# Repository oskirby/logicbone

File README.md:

LogicBone
=========

When you can't quite find the development board you want, why not make your own?

This project aims to design a feature rich FPGA development board that is
compatible with the open source FPGA synthesis tools such as [yosys](http://www.clifford.at/yosys/),
[NextPNR](https://github.com/YosysHQ/nextpnr) and [SymbiFlow](https://github.com/SymbiFlow),
while also targeting larger logic designs that need faster IO. The
requirements set out for this board are, in order of priority:
 * Compatiblity with open-source FPGA synthesis tools.
 * Minimum of 4Gb of high speed memory, preferably at least 8Gb.
 * At least one Ethernet interface.
 * Compatiblity with existing expansion interfaces.
 * USB interface for programming, debug and power.
 * Licenseable as Open Source Hardware.

The ultimate objective of this board is to instantiate a soft core processor, such as
the RISC-V, and use it to boot a Linux operating system with networking.

To that effect, this board is designed to be mechanically and electrically compatible
with the Beaglebone Black, but featuring a Lattice ECP5 FPGA, which is available in
logic sizes up to 85k LUTs, and a selection of hardware blocks for DDR3 DQS acceleration,
MIPI interfaces, DSPs and 3Gbps SERDES.

Features
--------

The major features of this board include:
 * Lattice ECP5 (LFE5UM5G-45F-8BG381C)
   - 44k LUTs and 351 kbits of distributed RAM 
   - 1944 kbits of embedded block RAM
   - 203 IO pins
   - 72 hardware multipliers
   - 4 PLLs
   - 2 dual channel 5Gbps SERDES
 * Beaglebone Black mechanical and header compatibility.
   - P9 is fully connected to the FPGA.
   - P8 has 32 pins connected to the FPGA.
   - 12-bit 1MSPS muxed ADC on P9 analog pins.
 * 8Gb on-board DDR3L RAM
 * KSZ9031 Gigabit Ethernet PHY
 * microSD card slot
 * USB-C upstream facing port for power and programming
 * USB-C downstream facing port with USB Superspeed support
 * M.2 E-Keyed expansion interface:
   - Accepts connectivity options in the 2230 form factor
   - Both PCIe lanes are routed to the FPGA SERDES
   - GPIO, UART, SDIO and PCM interfaces
 * MaxLinear MxL7704 power manager

Work In Progress
----------------
This project has completed the PCB layout phase, and we are moving into hardware
prototyping. While we wait for the first boards to arrive, we have a 
[schematic](logicbone.pdf) and some renders of the board that might satisfy your
curiosity.

We would be happy to accept any feedback and review on the design that you
might be willing to provide.

Copyright
---------
Copyright Owen Kirby 2020

This documentation describes Open Hardware and is licensed under the
CERN OHL v1.2.

You may redistribute and modify this documentation under the terms of
the CERN OHL v1.2. (see [LICENSE.txt](LICENSE.txt)). This documentation
is distributed WITHOUT ANY EXPRESS OR IMPLIED WARRANTY, INCLUDING OF
MERCHANTABILITY, SATISFACTORY QUALITY AND FITNESS FOR A PARTICULAR
PURPOSE. Please see the CERN OHL v.1.2 for applicable conditions.

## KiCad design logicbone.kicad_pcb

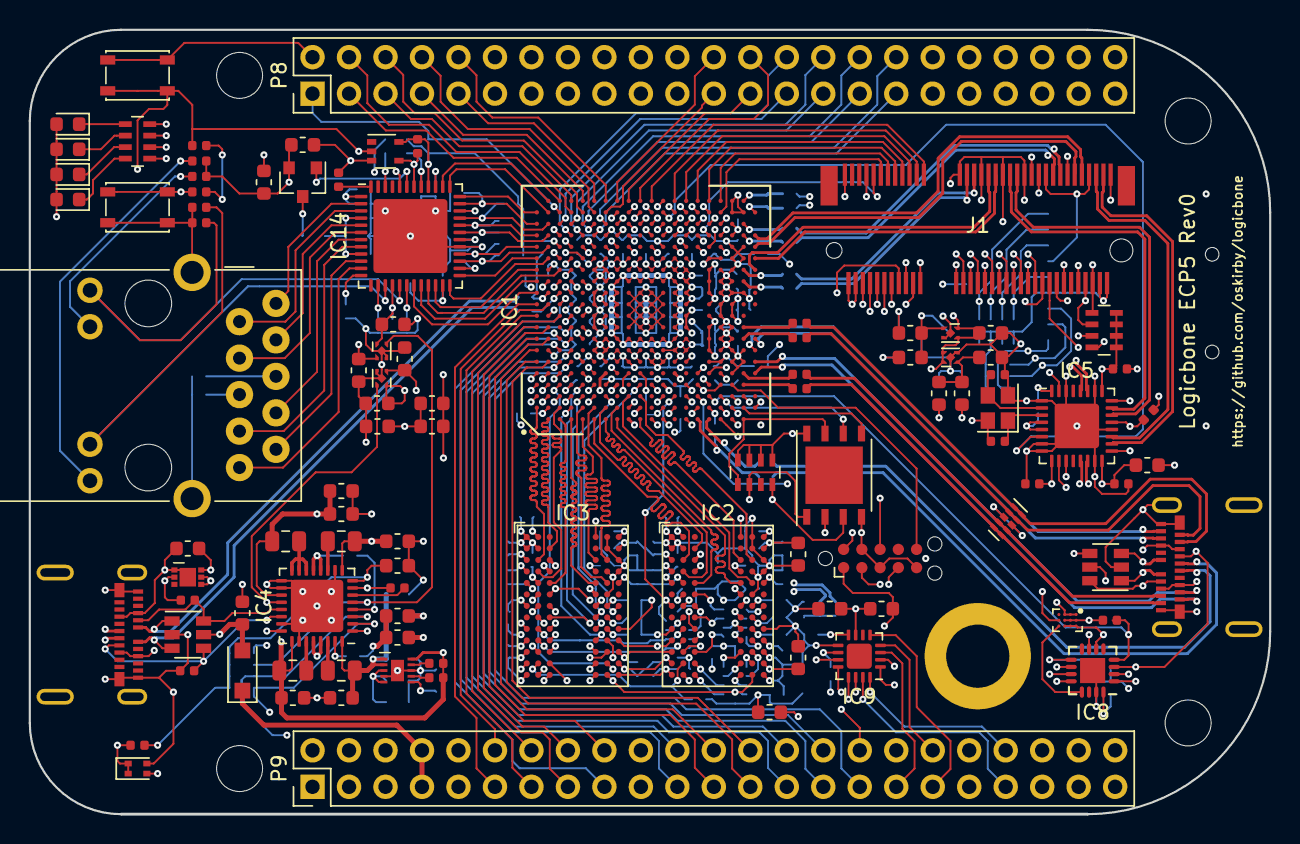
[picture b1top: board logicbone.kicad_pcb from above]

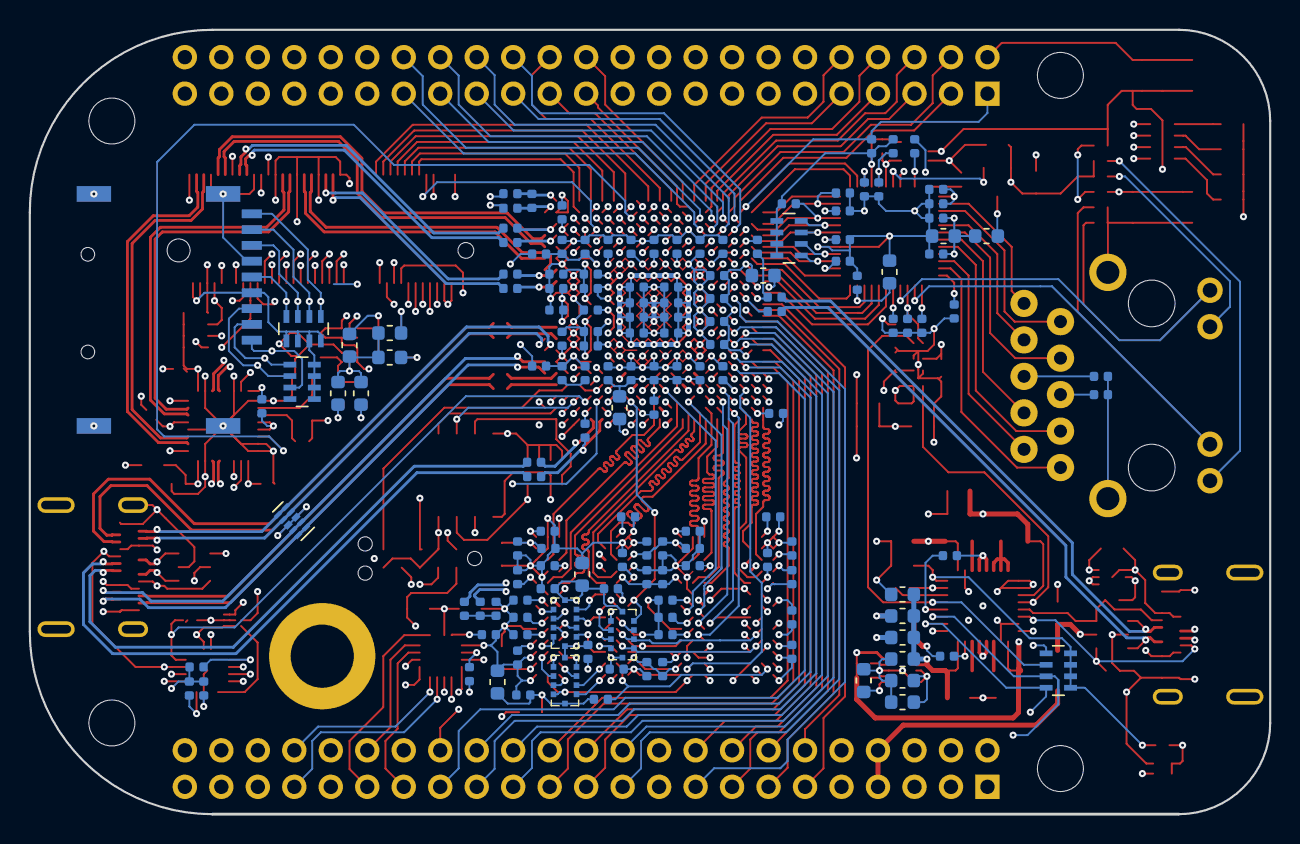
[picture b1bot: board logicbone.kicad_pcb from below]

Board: 8 copper layers, 86.4 x 54.6 mm, 255 parts (150 on the bottom side), 310 nets.

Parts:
C1, C108, C109: C_Small; C_0402_1005Metric
C2, C3, C8, C9, C10, C11, C110, C111, C112, C113, C114, C115, C116, C118, C120, C121, C122, C123, C201, C202, C210, C211, C221, C222, C230, C231, C257, C260, C261, C264, C265, C266, C280, C300, C301, C302, C309, C310, C311, C316, C317, C318, C319, C401, C402, C403, C411, C412, C421, C422, C423, C431, C432, C451, C452, C454, C455, C456, C461, C462, C463, C464, C465, C467, C469, C500, C501, C502, C504, C514, C517, C522, C527: 100nF; C_0402_1005Metric
C4, C258, C404, C405, C406, C414, C415, C416, C424, C425, C426, C434, C435, C436, C505, C506, C508, C509, C512, C513, C515, C516, C520, C521, C525, C526: 10nF; C_0402_1005Metric
C5, C100, C101, C102, C104, C117, C150, C151, C152, C154, C155, C156, C158, C159, C160, C161, C162, C163, C164, C165, C166, C167, C170, C171, C255, C303, C304, C308, C315, C400, C410, C420, C430, C440, C441, C442, C443, C445, C460, C524, C529: 10uF; C_0603_1608Metric
C6, C259, C305, C306, C307, C312, C313, C314: 1nF; C_0402_1005Metric
C7: 1uF; C_0603_1608Metric
D1: LED_Dual_ACAC; LED_0603_DUAL
D2, D3, D4, D5: LED_ALT; LED_0603_1608Metric
D6: D_Schottky_ALT; D_SOD-123F
D7, D8: D5V0F4U6SO; SOT-23-6
D9, D10: TPD4E02B04; USON-10_2.5x1.0mm_P0.5mm
FB1, FB2, FB3, FB4, FB5, FB7, FB8, FB9: MPZ1608S600; L_0603_1608Metric
H1, H2, H3, H4: MountingHole; MountingHole_3.2mm_M3
H5: MountingHole_Pad; wurth-9774025360
IC1: ECP5UM-CABGA381; caBGA-381_20x20_17.0x17.0mm
IC2, IC3: DDR3-TFBGA78; FBGA-78_7.5x11mm_Layout2x3x13_P0.8mm
IC4: MXL7704; QFN-32-1EP_5x5mm_P0.5mm_EP3.65x3.65mm
IC5: PI6CG18401; QFN-32-1EP_5x5mm_P0.5mm_EP3.1x3.1mm
IC6: NCP349; DFN6_1.6x2mm
IC7: FPF2595; WLCSP-12_3x4_1.3x1.8mm
IC8: FUSB307; UQFN-16-1EP_3x3mm_P0.5mm_EP1.75x1.75mm
IC9: TLA2518; WQFN-16-1EP_3x3mm_P0.5mm_EP1.75x1.75mm
IC10: AT25SL128A; DFN-8-1EP_6x5mm_P1.27mm_EP4x4mm
IC12: 74LVC1G07; SOT-353_SC-70-5
IC13: TPS51206; WSON-10EP-2x2mm
IC14: KSZ9031RNXCA; QFN-48-1EP_7x7mm_P0.5mm_EP5.15x5.15mm
IC17, IC18: NCP110AMX110; UDFN-4-1EP_1x1mm_P0.65mm_EP0.48x0.48mm
IC19, IC20: NCP115AMX250; UDFN-4-1EP_1x1mm_P0.65mm_EP0.48x0.48mm
J1: NGFF-KEY-E; TE-2199119-4
J2, J5: USB_C_Receptacle; Molex-1054500101
J3: ARJM11xx-502; ARJM11B1_502
J4: TC2050-IDC-NL; Tag-Connect_TC2050-IDC-NL_2x05_P1.27mm_Vertical
J6: Micro_SD_MEM2075; MEM2075
L1: 2.2uH; L_0805_2012Metric
L2, L4: 0.47uH; L_0805_2012Metric
L3: 1uH; L_0805_2012Metric
P8, P9: BB_2x23; PinHeader_2x23_P2.54mm_Vertical
Q1: Q_PMOS_GSD; SOT-23
R1, R2, R6, R37: 20; R_0402_1005Metric
R3, R4: 240; R_0402_1005Metric
R5: 100; R_0402_1005Metric
R7: 12.1k; R_0402_1005Metric
R8, R13, R18, R20, R21, R22, R23, R24, R25, R30, R31, R32, R35: 10k; R_0402_1005Metric
R9, R14, R15, R16: 47; R_0402_1005Metric
R10: 470; R_0402_1005Metric
R11, R12: 5.1k; R_0402_1005Metric
R17, R26: 1.5k; R_0402_1005Metric
R19, R29: 4.7k; R_0402_1005Metric
R27, R28: R; R_0402_1005Metric
R33: 750; R_0402_1005Metric
R34, R36: 1.2k; R_0402_1005Metric
RN1, RN2, RN3: 47; EXBD-1206
RN4, RN5, RN7: 4.7k; R_Array_Concave_4x0603
RN6, RN8, RN11: 10k; R_Array_Concave_4x0603
RN9: 470; R_Array_Concave_4x0603
SW1, SW2: SW_SPST; SW_SPST_PTS810
Y1: 25MHz; Crystal_SMD_2520-4Pin_2.5x2.0mm

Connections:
+3V3: C100.1, IC4.1, IC4.8, R10.2, R19.1, R29.1, RN5.5, RN5.6, RN5.7, RN5.8
/DDR3 Power/VDDR_CORE: C400.1, C401.1, C402.1, C403.1, C404.1, C405.1, C406.1, C420.1, C421.1, C422.1, C423.1, C424.1, C425.1, C426.1, FB9.2, IC2.A2, IC2.A9, IC2.D7, IC2.G2, IC2.G8, IC2.K1, IC2.K9, IC2.M1, IC2.M9, IC3.A2, IC3.A9, IC3.D7, IC3.G2, IC3.G8, IC3.K1, IC3.K9, IC3.M1, IC3.M9
/DDR3 Power/VDDR_IO: C410.1, C411.1, C412.1, C414.1, C415.1, C416.1, C430.1, C431.1, C432.1, C434.1, C435.1, C436.1, FB8.2, IC2.B9, IC2.C1, IC2.E2, IC2.E9, IC3.B9, IC3.C1, IC3.E2, IC3.E9
/Ethernet/25M_REFCLK: C2.1, IC1.M19, IC5.6
/Ethernet/ETH_1V2: C308.1, C309.1, C310.1, C311.1, C312.1, C313.1, C314.1, FB7.2, IC14.14, IC14.18, IC14.23, IC14.26, IC14.30, IC14.39, Q1.3
/Ethernet/ETH_AVDDL: C315.1, C316.1, C317.1, FB7.1, IC14.4, IC14.9, IC14.44
/Ethernet/ETH_LDO: IC14.43, Q1.1
/Ethernet/ETH_LED_L: IC14.15, J3.L2, R24.2
/Ethernet/ETH_LED_R: IC14.17, J3.L4, R25.2
/Ethernet/ETH_REFCLK: IC1.D12, IC14.41, R21.2, R22.2
/Ethernet/ETH_RXCLK: IC1.A18, IC14.35, R23.2
/Ethernet/ETH_RXCTL: IC1.B18, IC14.33, R20.2
/Ethernet/ETH_RXD0: IC1.A17, IC14.32, RN11.4
/Ethernet/ETH_RXD1: IC1.B17, IC14.31, RN11.3
/Ethernet/ETH_RXD2: IC1.A16, IC14.28, RN11.2
/Ethernet/ETH_RXD3: IC1.B16, IC14.27, RN11.1
/Ethernet/ETH_TRXD1N: IC14.3, J3.2
/Ethernet/ETH_TRXD1P: IC14.2, J3.1
/Ethernet/ETH_TRXD2N: IC14.6, J3.4
/Ethernet/ETH_TRXD2P: IC14.5, J3.3
/Ethernet/ETH_TRXD3N: IC14.8, J3.8
/Ethernet/ETH_TRXD3P: IC14.7, J3.7
/Ethernet/ETH_TRXD4N: IC14.11, J3.10
/Ethernet/ETH_TRXD4P: IC14.10, J3.9
/Ethernet/ETH_TXCLK: IC1.B15, IC14.24
/Ethernet/ETH_TXCTL: IC1.A15, IC14.25
/Ethernet/ETH_TXD0: IC1.A12, IC14.19
/Ethernet/ETH_TXD1: IC1.A13, IC14.20
/Ethernet/ETH_TXD2: IC1.C14, IC14.21
/Ethernet/ETH_TXD3: IC1.A14, IC14.22
/Ethernet/FPGA_USB+: D7.1, J2.A6, J2.B6, R1.1
/Ethernet/FPGA_USB-: D7.3, J2.A7, J2.B7, R2.1
/Ethernet/FPGA_USB_PULL: IC1.C16, R26.2
/Ethernet/LED_USER1: IC1.D16, J1.6, RN9.8
/Ethernet/LED_USER2: IC1.C15, J1.16, RN9.7
/Ethernet/LED_USER3: IC1.C13, RN9.6
/Ethernet/LED_USER4: IC1.B13, RN9.5
/Ethernet/MDIO_CLK: IC1.A19, IC14.36
/Ethernet/MDIO_DATA: IC1.B19, IC14.37
/Ethernet/MMC_CLK: IC1.E11, J6.5, RN6.4
/Ethernet/MMC_CMD: IC1.D15, J6.3, RN8.6
/Ethernet/MMC_DAT0: IC1.D13, J6.7, RN6.3
/Ethernet/MMC_DAT1: IC1.E13, J6.8, RN6.2
/Ethernet/MMC_DAT2: IC1.E15, J6.1, RN8.7
/Ethernet/MMC_DAT3: IC1.E14, J6.2, RN8.5
/Ethernet/MMC_DET: IC1.D14, J6.9, RN6.1
/Ethernet/~ETH_INT: IC1.B20, IC14.38
/Ethernet/~ETH_RESET: IC1.C17, IC12.4, IC14.42, R13.2
/Ethernet/~SYS_RESET: IC1.W3, IC12.2, J4.10, P9.10, R19.2, SW2.1
/Exp Headers/ADC_MISO: IC1.E8, IC9.12
/Exp Headers/ADC_MOSI: IC1.D10, IC9.14
/Exp Headers/ADC_SCLK: IC1.E9, IC9.13
/Exp Headers/P8_LVDS1n: IC1.D19, P8.4
/Exp Headers/P8_LVDS1p: IC1.C20, P8.3
/Exp Headers/P8_LVDS2n: IC1.E19, P8.6
/Exp Headers/P8_LVDS2p: IC1.D20, P8.5
/Exp Headers/P8_LVDS3n: IC1.F19, P8.8
/Exp Headers/P8_LVDS3p: IC1.E20, P8.7
/Exp Headers/P8_LVDS4n: IC1.G20, P8.10
/Exp Headers/P8_LVDS4p: IC1.F20, P8.9
/Exp Headers/P8_LVDS5n: IC1.H20, P8.24
/Exp Headers/P8_LVDS5p: IC1.G19, P8.23
/Exp Headers/P8_LVDS6n: IC1.K20, P8.26
/Exp Headers/P8_LVDS6p: IC1.J20, P8.25
/Exp Headers/P8_LVDS7n: IC1.D17, P8.28
/Exp Headers/P8_LVDS7p: IC1.C18, P8.27
/Exp Headers/P8_LVDS8n: IC1.E17, P8.30
/Exp Headers/P8_LVDS8p: IC1.D18, P8.29
/Exp Headers/P8_LVDS9n: IC1.F18, P8.32
/Exp Headers/P8_LVDS9p: IC1.E18, P8.31
/Exp Headers/P8_LVDS10n: IC1.G18, P8.34
/Exp Headers/P8_LVDS10p: IC1.F17, P8.33
/Exp Headers/P8_LVDS11n: IC1.F16, P8.36
/Exp Headers/P8_LVDS11p: IC1.E16, P8.35
/Exp Headers/P8_LVDS12n: IC1.H16, P8.38
/Exp Headers/P8_LVDS12p: IC1.G16, P8.37
/Exp Headers/P8_LVDS13n: IC1.J16, P8.40
/Exp Headers/P8_LVDS13p: IC1.J17, P8.39
/Exp Headers/P8_LVDS14n: IC1.H17, P8.42
/Exp Headers/P8_LVDS14p: IC1.H18, P8.41
/Exp Headers/P8_LVDS15n: IC1.K19, P8.44
/Exp Headers/P8_LVDS15p: IC1.J19, P8.43
/Exp Headers/P8_LVDS16n: IC1.K18, P8.46
/Exp Headers/P8_LVDS16p: IC1.J18, P8.45
/Exp Headers/P9_AIN0: IC9.15, P9.39
/Exp Headers/P9_AIN1: IC9.16, P9.40
/Exp Headers/P9_AIN2: IC9.1, P9.37
/Exp Headers/P9_AIN3: IC9.2, P9.38
/Exp Headers/P9_AIN4: IC9.3, P9.33
/Exp Headers/P9_AIN5: IC9.4, P9.36
/Exp Headers/P9_AIN6: IC9.5, P9.35
/Exp Headers/P9_CLKOUT: IC1.B10, P9.41
/Exp Headers/P9_GPIO11: IC1.A11, P9.11
/Exp Headers/P9_GPIO12: IC1.B11, P9.12
/Exp Headers/P9_GPIO13: IC1.A10, P9.13
/Exp Headers/P9_GPIO14: IC1.C10, P9.14
/Exp Headers/P9_GPIO15: IC1.A9, P9.15
/Exp Headers/P9_GPIO16: IC1.B9, P9.16
/Exp Headers/P9_GPIO17: IC1.C11, P9.17
/Exp Headers/P9_GPIO18: IC1.A8, P9.18
/Exp Headers/P9_GPIO21: IC1.D9, P9.21
/Exp Headers/P9_GPIO22: IC1.C8, P9.22
/Exp Headers/P9_GPIO23: IC1.B8, P9.23
/Exp Headers/P9_GPIO24: IC1.A7, P9.24
/Exp Headers/P9_GPIO25: IC1.A6, P9.25
/Exp Headers/P9_GPIO26: IC1.B6, P9.26
/Exp Headers/P9_GPIO27: IC1.D8, P9.27
/Exp Headers/P9_GPIO42: IC1.E10, P9.42
/Exp Headers/P9_SPI_D0: IC1.D7, P9.29
/Exp Headers/P9_SPI_D1: IC1.C6, P9.30
/Exp Headers/P9_SPI_SCLK: IC1.D6, P9.31
/Exp Headers/PWR_BUTTON: IC1.U2, P9.9, R29.2, SW1.1
/Exp Headers/SCL: IC1.U1, IC4.3, IC5.10, IC8.12, J1.60, P9.19, RN5.3
/Exp Headers/SDA: IC1.V1, IC4.2, IC5.11, IC8.11, J1.58, P9.20, RN5.4
/Exp Headers/SYS_5V: D6.1, P9.7, P9.8
/Exp Headers/~ADC_CSEL: IC1.E6, IC9.11
/Exp Headers/~P9_SPI_CSEL: IC1.C7, P9.28
/FPGA Memory/DDR3_A0: IC1.B4, IC2.K3, IC3.K3, RN3.3
/FPGA Memory/DDR3_A1: IC1.F4, IC2.L7, IC3.L7, RN2.2
/FPGA Memory/DDR3_A2: IC1.A4, IC2.L3, IC3.L3, RN1.9
/FPGA Memory/DDR3_A3: IC1.F3, IC2.K2, IC3.K2, RN3.9
/FPGA Memory/DDR3_A4: IC1.E5, IC2.L8, IC3.L8, RN2.8
/FPGA Memory/DDR3_A5: IC1.C5, IC2.L2, IC3.L2, RN3.2
/FPGA Memory/DDR3_A6: IC1.C4, IC2.M8, IC3.M8, RN2.9
/FPGA Memory/DDR3_A7: IC1.A5, IC2.M2, IC3.M2, R14.2
/FPGA Memory/DDR3_A8: IC1.A3, IC2.N8, IC3.N8, RN2.6
/FPGA Memory/DDR3_A9: IC1.B5, IC2.M3, IC3.M3, RN2.4
/FPGA Memory/DDR3_A10: IC1.G3, IC2.H7, IC3.H7, RN1.4
/FPGA Memory/DDR3_A11: IC1.D5, IC2.M7, IC3.M7, RN2.3
/FPGA Memory/DDR3_A12: IC1.D2, IC2.K7, IC3.K7, RN1.3
/FPGA Memory/DDR3_A13: IC1.F5, IC2.N3, IC3.N3, RN2.5
/FPGA Memory/DDR3_A14: IC1.D3, IC2.N7, IC3.N7, RN2.7
/FPGA Memory/DDR3_A15: IC1.E3, IC2.J7, IC3.J7, RN1.8
/FPGA Memory/DDR3_BA0: IC1.B3, IC2.J2, IC3.J2, RN3.8
/FPGA Memory/DDR3_BA1: IC1.H5, IC2.K8, IC3.K8, RN1.2
/FPGA Memory/DDR3_BA2: IC1.N2, IC2.J3, IC3.J3, RN3.5
/FPGA Memory/DDR3_CK+: IC1.M4, IC2.F7, IC3.F7, R15.2
/FPGA Memory/DDR3_CK-: IC1.N5, IC2.G7, IC3.G7, R16.1
/FPGA Memory/DDR3_CKE: IC1.K4, IC2.G9, IC3.G9, RN1.5
/FPGA Memory/DDR3_DM0: IC1.L4, IC2.A7
/FPGA Memory/DDR3_DM1: IC1.J5, IC3.A7
/FPGA Memory/DDR3_DQ0: IC1.G2, IC2.B3
/FPGA Memory/DDR3_DQ1: IC1.K1, IC2.C7
/FPGA Memory/DDR3_DQ2: IC1.F1, IC2.C2
/FPGA Memory/DDR3_DQ3: IC1.K3, IC2.C8
/FPGA Memory/DDR3_DQ4: IC1.H2, IC2.E3
/FPGA Memory/DDR3_DQ5: IC1.J3, IC2.E8
/FPGA Memory/DDR3_DQ6: IC1.G1, IC2.D2
/FPGA Memory/DDR3_DQ7: IC1.H1, IC2.E7
/FPGA Memory/DDR3_DQ8: IC1.B1, IC3.B3
/FPGA Memory/DDR3_DQ9: IC1.E1, IC3.C7
/FPGA Memory/DDR3_DQ10: IC1.A2, IC3.C2
/FPGA Memory/DDR3_DQ11: IC1.F2, IC3.C8
/FPGA Memory/DDR3_DQ12: IC1.C1, IC3.E3
/FPGA Memory/DDR3_DQ13: IC1.E2, IC3.E8
/FPGA Memory/DDR3_DQ14: IC1.C2, IC3.D2
/FPGA Memory/DDR3_DQ15: IC1.D1, IC3.E7
/FPGA Memory/DDR3_DQS0+: IC1.K2, IC2.C3
/FPGA Memory/DDR3_DQS0-: IC1.J1, IC2.D3
/FPGA Memory/DDR3_DQS1+: IC1.H4, IC3.C3
/FPGA Memory/DDR3_DQS1-: IC1.G5, IC3.D3
/FPGA Memory/DDR3_ODT0: IC1.N3, IC2.G1, RN3.6
/FPGA Memory/DDR3_ODT1: IC1.C3, IC3.G1, R9.1
/FPGA Memory/DDR3_VREF: C460.1, C461.1, C462.2, C463.1, C464.1, C465.1, C467.1, IC1.B2, IC1.K5, IC2.E1, IC2.J8, IC3.E1, IC3.J8, IC13.6
/FPGA Memory/~DDR3_CAS: IC1.M1, IC2.G3, IC3.G3, RN3.4
/FPGA Memory/~DDR3_CS: IC1.M3, IC2.H2, IC3.H2, RN3.7
/FPGA Memory/~DDR3_RAS: IC1.L1, IC2.F3, IC3.F3, RN1.6
/FPGA Memory/~DDR3_RST: IC1.P1, IC2.N2, IC3.N2
/FPGA Memory/~DDR3_WE: IC1.E4, IC2.H3, IC3.H3, RN1.7
/FPGA Power/PGOOD: D1.1, D1.3, IC4.20, IC20.3, R10.1, RN5.1
/FPGA Power/PMIC_ENABLE: IC4.6, R32.1
/FPGA Power/PMIC_PG1: IC4.5, IC19.3, RN5.2
/FPGA Power/PMIC_SEQ: IC4.4, R18.2
/FPGA Power/USB_UFP_CC1: D7.6, IC4.21, J2.A5, R12.2
/FPGA Power/USB_UFP_CC2: D7.4, IC4.22, J2.B5, R11.1
/FPGA Power/VCCA0: C520.1, C521.1, C522.1, C524.1, FB2.2, IC1.T6, IC1.U6
/FPGA Power/VCCA1: C525.1, C526.1, C527.1, C529.1, FB3.2, IC1.T15, IC1.U15
/FPGA SERDES/FPGA_REFCLK+: IC1.P3, IC5.13
/FPGA SERDES/FPGA_REFCLK-: IC1.P4, IC5.14
/FPGA SERDES/M2_COEX1: IC1.P18, J1.44
/FPGA SERDES/M2_COEX2: IC1.P19, J1.46
/FPGA SERDES/M2_COEX3: IC1.N17, J1.48
/FPGA SERDES/M2_CTS: IC1.R18, J1.34
/FPGA SERDES/M2_PCM_CLK: IC1.U16, J1.8
/FPGA SERDES/M2_PCM_IN: IC1.P16, J1.12
/FPGA SERDES/M2_PCM_OUT: IC1.T16, J1.14
/FPGA SERDES/M2_PCM_SYNC: IC1.N16, J1.10
/FPGA SERDES/M2_RTS: IC1.U18, J1.36
/FPGA SERDES/M2_RXD: IC1.R17, J1.22
/FPGA SERDES/M2_SDIO_CLK: IC1.T17, J1.9
/FPGA SERDES/M2_SDIO_CMD: IC1.U19, J1.11
/FPGA SERDES/M2_SDIO_DATA0: IC1.U20, J1.13
/FPGA SERDES/M2_SDIO_DATA1: IC1.T20, J1.15
/FPGA SERDES/M2_SDIO_DATA2: IC1.R20, J1.17
/FPGA SERDES/M2_SDIO_DATA3: IC1.P20, J1.19
/FPGA SERDES/M2_SUSCLK: IC1.L16, J1.50
/FPGA SERDES/M2_TXD: IC1.U17, J1.32
/FPGA SERDES/M2_VEND0: IC1.N18, J1.42
/FPGA SERDES/M2_VEND1: IC1.T19, J1.40
/FPGA SERDES/M2_VEND2: IC1.P17, J1.38
/FPGA SERDES/PCIE_REFCLK0+: IC5.23, J1.47
/FPGA SERDES/PCIE_REFCLK0-: IC5.22, J1.49
/FPGA SERDES/PCIE_REFCLK1+: IC5.19, J1.71
/FPGA SERDES/PCIE_REFCLK1-: IC5.18, J1.73
/FPGA SERDES/PCIE_RX0+: IC1.Y14, J1.41
/FPGA SERDES/PCIE_RX0-: IC1.Y15, J1.43
/FPGA SERDES/PCIE_RX1+: IC1.Y16, J1.65
/FPGA SERDES/PCIE_RX1-: IC1.Y17, J1.67
/FPGA SERDES/PCIE_TX0+: C115.2, J1.35
/FPGA SERDES/PCIE_TX0-: C114.2, J1.37
/FPGA SERDES/PCIE_TX1+: C113.2, J1.59
/FPGA SERDES/PCIE_TX1-: C112.2, J1.61
/FPGA SERDES/SERDES_REFCLK+: C111.2, IC5.28
/FPGA SERDES/SERDES_REFCLK-: C110.2, IC5.27
/FPGA SERDES/VCCTRX1: C255.1, C257.1, C258.1, C259.1, FB5.1, IC1.T11, IC1.T12, IC1.T13, IC1.T14
/FPGA SERDES/~M2_ALERT: IC1.L19, J1.62
/FPGA SERDES/~M2_SDIO_RESET: IC1.L20, J1.23
/FPGA SERDES/~M2_SDIO_WAKE: IC1.N20, J1.21
/FPGA SERDES/~M2_UART_WAKE: IC1.T18, J1.20
/FPGA SERDES/~M2_WDIS1: IC1.L17, J1.56
/FPGA SERDES/~M2_WDIS2: IC1.M18, J1.54
/FPGA SERDES/~PCIE_CLKREQ0: IC5.24, J1.53, RN4.4
/FPGA SERDES/~PCIE_CLKREQ1: IC5.17, J1.68, RN4.2
/FPGA SERDES/~PCIE_RESET0: IC1.M17, J1.52
/FPGA SERDES/~PCIE_RESET1: IC1.N19, J1.66
/FPGA SERDES/~PCIE_WAKE0: IC1.L18, J1.55, RN4.3
/FPGA SERDES/~PCIE_WAKE1: IC1.M20, J1.70, RN4.1
/USB and Programming/DFP_SOURCE_EN: IC7.D3, IC8.13
/USB and Programming/FLASH_D2: IC1.Y2, IC10.3, RN7.4
/USB and Programming/FLASH_D3: IC1.W1, IC10.7, RN7.1
/USB and Programming/FLASH_MISO: IC1.V2, IC10.2
/USB and Programming/FLASH_MOSI: IC1.W2, IC10.5
/USB and Programming/FLASH_SCLK: IC1.U3, IC10.6
/USB and Programming/FPGA_TCK: IC1.T5, J4.4
/USB and Programming/FPGA_TDI: IC1.R5, J4.8
/USB and Programming/FPGA_TDO: IC1.V4, J4.6
/USB and Programming/FPGA_TMS: IC1.U5, J4.2
/USB and Programming/FPGA_USB_DFP+: IC1.R1, R6.1, R17.2
/USB and Programming/FPGA_USB_DFP-: IC1.T1, R37.2
/USB and Programming/USBC_DFP+: D8.1, J5.A6, J5.B6, R6.2
/USB and Programming/USBC_DFP-: D8.3, J5.A7, J5.B7, R37.1
/USB and Programming/USBSS_RX1+: D10.1, D10.10, IC1.Y5, J5.B11
/USB and Programming/USBSS_RX1-: D10.2, D10.9, IC1.Y6, J5.B10
/USB and Programming/USBSS_RX2+: D10.5, D10.6, IC1.Y7, J5.A11
/USB and Programming/USBSS_RX2-: D10.4, D10.7, IC1.Y8, J5.A10
/USB and Programming/USBSS_TX1+: C8.2, D9.5, D9.6, J5.A2
/USB and Programming/USBSS_TX1-: C9.2, D9.4, D9.7, J5.A3
/USB and Programming/USBSS_TX2+: C10.2, D9.2, D9.9, J5.B2
/USB and Programming/USBSS_TX2-: C11.2, D9.1, D9.10, J5.B3
/USB and Programming/USB_DFP_CC1: D8.6, IC8.1, J5.A5
/USB and Programming/USB_DFP_CC2: D8.4, IC8.3, J5.B5
/USB and Programming/USB_DFP_PULL: IC1.T2, R17.1
/USB and Programming/USB_DFP_VBUS: IC7.A3, IC7.B3, IC7.C3, IC8.6, J5.A4, J5.A9, J5.B4, J5.B9
/USB and Programming/USB_ORIENT: IC1.T3, IC8.4, R35.2
/USB and Programming/VCCTRX0: C3.1, C4.1, C5.1, C6.1, FB4.1, IC1.T7, IC1.T8, IC1.T9, IC1.T10
/USB and Programming/~FLASH_CSEL: IC1.R2, IC10.1, RN7.2
/USB and Programming/~FPGA_INIT: D1.4, IC1.V3
/USB and Programming/~USB_INT: IC1.R3, IC8.10
GND: C1.2, C3.2, C4.2, C5.2, C6.2, C7.2, C100.2, C101.2, C102.2, C104.2, C108.2, C109.2, C116.2, C117.2, C118.2, C120.2, C121.2, C122.2, C123.2, C150.2, C151.2, C152.2, C154.2, C155.2, C156.2, C158.2, C159.2, C160.2, C161.2, C162.2, C163.2, C164.2, C165.2, C166.2, C167.2, C170.2, C171.2, C201.2, C202.2, C210.2, C211.2, C221.2, C222.2, C230.2, C231.2, C255.2, C257.2, C258.2, C259.2, C260.2, C261.2, C264.2, C265.2, C266.2, C280.2, C300.2, C301.2, C302.2, C303.2, C304.2, C305.2, C306.2, C307.2, C308.2, C309.2, C310.2, C311.2, C312.2, C313.2, C314.2, C315.2, C316.2, C317.2, C318.2, C319.2, C400.2, C401.2, C402.2, C403.2, C404.2, C405.2, C406.2, C410.2, C411.2, C412.2, C414.2, C415.2, C416.2, C420.2, C421.2, C422.2, C423.2, C424.2, C425.2, C426.2, C430.2, C431.2, C432.2, C434.2, C435.2, C436.2, C440.2, C441.2, C442.2, C443.2, C445.2, C451.2, C452.2, C454.2, C455.2, C456.2, C460.2, C461.2, C462.1, C463.2, C464.2, C465.2, C467.2, C469.2, C500.2, C501.2, C502.2, C504.2, C505.2, C506.2, C508.2, C509.2, C512.2, C513.2, C514.2, C515.2, C516.2, C517.2, C520.2, C521.2, C522.2, C524.2, C525.2, C526.2, C527.2, C529.2, D1.2, D7.2, D8.2, D9.3, D9.8, D10.3, D10.8, H5.1, IC1.B7, IC1.B14, IC1.C19, IC1.D4, IC1.F7, IC1.F8, IC1.F13, IC1.F14, IC1.G4, IC1.G6, IC1.G7, IC1.G8, IC1.G9, IC1.G10, IC1.G11, IC1.G12, IC1.G13, IC1.G14, IC1.G15, IC1.G17, IC1.H19, IC1.J2, IC1.J7, IC1.J9, IC1.J10, IC1.J11, IC1.J12, IC1.J14, IC1.K6, IC1.K7, IC1.K9, IC1.K10, IC1.K11, IC1.K12, IC1.K14, IC1.K15, IC1.L9, IC1.L10, IC1.L11, IC1.L12, IC1.M2, IC1.M7, IC1.M9, IC1.M10, IC1.M11, IC1.M12, IC1.M14, IC1.M16, IC1.N6, IC1.N7, IC1.N14, IC1.N15, IC1.P7, IC1.P8, IC1.P11, IC1.P12, IC1.P13, IC1.P14, IC1.R4, IC1.R19, IC1.U4, IC1.U7, IC1.U8, IC1.U9, IC1.U10, IC1.U11, IC1.U12, IC1.U13, IC1.U14, IC1.V5, IC1.V6, IC1.V7, IC1.V8, IC1.V9, IC1.V12, IC1.V13, IC1.V14, IC1.V15, IC1.V16, IC1.V19, IC1.V20, IC1.W6, IC1.W7, IC1.W12, IC1.W15, IC1.W16, IC1.W19, IC2.A1, IC2.A8, IC2.B1, IC2.B2, IC2.B8, IC2.C9, IC2.D1, IC2.D8, IC2.D9, IC2.F2, IC2.F8, IC2.J1, IC2.J9, IC2.L1, IC2.L9, IC2.N1, IC2.N9, IC3.A1, IC3.A8, IC3.B1, IC3.B2, IC3.B8, IC3.C9, IC3.D1, IC3.D8, IC3.D9, IC3.F2, IC3.F8, IC3.J1, IC3.J9, IC3.L1, IC3.L9, IC3.N1, IC3.N9, IC4.10, IC4.17, IC4.18, IC4.23, IC4.26, IC4.33, IC5.1, IC5.7, IC5.8, IC5.15, IC5.20, IC5.26, IC5.30, IC5.33, IC6.2, IC6.6, IC7.A2, IC7.B2, IC7.C2, IC8.15, IC8.17, IC9.9, IC10.4, IC12.3, IC13.4, IC13.8, IC13.11, IC14.29, IC14.49, IC17.2, IC17.5, IC18.2, IC18.5, IC19.2, IC19.5, IC20.2, IC20.5, J1.1, J1.7, J1.18, J1.33, J1.39, J1.45, J1.51, J1.57, J1.63, J1.69, J1.75, J2.A1, J2.A12, J2.B1, J2.B12, J2.S1, J3.SH, J4.3, J4.5, J4.9, J5.A1, J5.A12, J5.B1, J5.B12, J5.S1, J6.6, J6.10, P8.1, P8.2, P9.1, P9.2, P9.34, P9.43, P9.44, P9.45, P9.46, R3.2, R4.2, R7.1, R11.2, R12.1, R22.1, R23.1, R24.1, R25.1, R35.1, R36.1, SW1.2, SW2.2, Y1.2, Y1.4
unnamed: C1.1, IC4.24, IC4.31
unnamed: C2.2, IC14.46
unnamed: C7.1, IC6.1, IC6.7, J2.A4, J2.A9, J2.B4, J2.B9
unnamed: C8.1, IC1.W4
unnamed: C9.1, IC1.W5
unnamed: C10.1, IC1.W8
unnamed: C11.1, IC1.W9
unnamed: C108.1, IC5.3, Y1.1
unnamed: C109.1, IC5.2, Y1.3
unnamed: C110.1, IC1.W20, R5.2
unnamed: C111.1, IC1.Y19, R5.1
unnamed: C112.1, IC1.W18
unnamed: C113.1, IC1.W17
unnamed: C114.1, IC1.W14
unnamed: C115.1, IC1.W13
unnamed: C116.1, IC9.8
unnamed: C117.1, FB1.1, IC9.7
unnamed: C318.1, J3.5
unnamed: C319.1, J3.6
unnamed: C469.1, R15.1, R16.2
unnamed: D2.1, RN9.1
unnamed: D3.1, RN9.2
unnamed: D4.1, RN9.3
unnamed: D5.1, RN9.4
unnamed: IC1.B12, R1.2, R26.1
unnamed: IC1.C12, R2.2
unnamed: IC2.H8, R3.1
unnamed: IC3.H8, R4.1
unnamed: IC4.11, L3.1
unnamed: IC4.14, IC4.15, IC4.16, L2.1
unnamed: IC4.27, L1.1
unnamed: IC4.30, L4.1
unnamed: IC5.32, R8.2
unnamed: IC7.D2, R33.2, R34.2, R36.2
unnamed: IC8.9, R33.1
unnamed: IC8.16, R34.1
unnamed: IC13.7, R31.1
unnamed: IC13.9, R30.1
unnamed: IC14.48, R7.2
unnamed: J3.L1, R27.2
unnamed: J3.L3, R28.2
VBUS: C104.1, D6.2, D7.5, D8.5, IC4.7, IC4.12, IC4.13, IC4.28, IC4.29, IC6.4, IC6.5, IC7.A1, IC7.B1, IC7.C1, P9.5, P9.6, R18.1, R32.2
VCC1V8: C120.1, C121.1, C122.1, C123.1, C163.1, C164.1, C165.1, C230.1, C231.1, IC1.L14, IC1.L15, IC1.M15, IC4.9, IC5.4, IC5.5, IC5.9, IC5.16, IC5.21, IC5.25, IC5.31, IC17.3, IC17.4, IC18.3, IC18.4, L3.2, P9.32, R8.1, RN4.5, RN4.6, RN4.7, RN4.8
VCC3V3: C118.1, C158.1, C160.1, C161.1, C201.1, C202.1, C210.1, C211.1, C221.1, C222.1, C280.1, C300.1, C301.1, C302.1, C303.1, C304.1, C305.1, C306.1, C307.1, D2.2, D3.2, D4.2, D5.2, FB1.2, IC1.F9, IC1.F10, IC1.F11, IC1.F12, IC1.H14, IC1.H15, IC1.J15, IC1.P9, IC1.P10, IC1.T4, IC4.25, IC8.2, IC8.7, IC9.10, IC10.8, IC12.5, IC13.10, IC14.1, IC14.12, IC14.16, IC14.34, IC14.40, IC19.4, IC20.4, J1.2, J1.4, J1.72, J1.74, J4.1, J6.4, L1.2, P9.3, P9.4, Q1.2, R13.1, R20.1, R21.1, R27.1, R28.1, R30.2, R31.2, RN6.5, RN6.6, RN6.7, RN6.8, RN7.5, RN7.6, RN7.7, RN7.8, RN8.1, RN8.2, RN8.3, RN8.4, RN11.5, RN11.6, RN11.7, RN11.8
VCCAUX: C166.1, C512.1, C513.1, C514.1, IC1.F6, IC1.F15, IC1.P6, IC1.P15, IC20.1
VCCAUXTRX: C167.1, C515.1, C516.1, C517.1, IC1.V10, IC1.V11, IC1.V17, IC1.V18, IC19.1
VCCTRX: C170.1, FB4.2, FB5.2, IC17.1
VCCTRXA: C171.1, FB2.1, FB3.1, IC18.1
VCORE: C101.1, C150.1, C151.1, C152.1, C159.1, C162.1, C500.1, C501.1, C502.1, C504.1, C505.1, C506.1, C508.1, C509.1, IC1.H8, IC1.H9, IC1.H10, IC1.H11, IC1.H12, IC1.H13, IC1.J8, IC1.J13, IC1.K8, IC1.K13, IC1.L8, IC1.L13, IC1.M8, IC1.M13, IC1.N8, IC1.N9, IC1.N10, IC1.N11, IC1.N12, IC1.N13, IC4.19, L2.2
VDDR: C102.1, C154.1, C155.1, C156.1, C260.1, C261.1, C264.1, C265.1, C266.1, FB8.1, FB9.1, IC1.H6, IC1.H7, IC1.J6, IC1.L6, IC1.L7, IC1.M6, IC4.32, IC13.1, IC13.2, L4.2
VTT: C440.1, C441.1, C442.1, C443.1, C445.1, C451.1, C452.1, C454.1, C455.1, C456.1, IC13.3, IC13.5, R9.2, R14.1, RN1.1, RN2.1, RN3.1

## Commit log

2019-12-14 Add ECP5UM-CABGA381 schematic symbol.
2019-12-28 Add major schematic components.
    This adds the bulk of the components to the schematic and performs an
    initial routing of signals to the FPGA, PMIC and Supervisor. This is
    still missing most, if not all, bypass capacitors.
2020-01-05 Finalize SERDES, exp headers, and start footprint association.
2020-01-13 Initial board outline and component placement.
2020-01-20 Revert back to a 16-bit DDR3 bus, initial DDR3 layout.
    The caBGA-554 package was too large and fat to reasonably be able
    to fit within the beaglebone footprint and still leave enough room
    for DDR3 and the expansion headers. So, it seems more sensible to
    switch back to a 16-bit wide bus.
    Now that we can fit everything, take a first stab at getting the DDR3
    data busses routed and length matched.
2020-02-02 Complete routing of the DDR interface.
    This is the last of the DDR3 signals connected, but we still need to
    revisit the length tuning.
2020-02-08 More routing progress on Ethernet and DDR.
2020-03-05 Routing of M.2 and PCIe, placed the Supervisor.
    Started work on getting the power supplies layed out too, and spent
    some time thinking about how the USB-C should connect up to the FPGA.
2020-03-06 Add CERN OHL license, and README.
2020-04-16 Replace PMIC with MXL7704, switch to SPI master programming.
    The Quorvo PMIC in the original design appears to have been deprecated
    on DigiKey. Out of concern for availability, let's switch to the MXL7704
    instead.
    In an effort to support to an FPGA-based bootloader solution, we have
    switched to using SPI master mode for the ECP5 configuration data. In
    the long run this might allow a considerable downsizing of the STM32.
2020-04-18 Add dedicated LDO for VCCAUX, and a bunch of cleanup
    The MXL7704 is almost capable of booting the entire ECP5 on its own
    without any help from the supervisor. So we would like to test it out
    on the prototype boards. To accompish this, we need to use a dedicated
    LDO for VCCAUX.
    With that, I am rapidly running out of major work to do and from here
    on out it's just going to be review and minor tweaks.
2020-04-19 Place VTT bypass caps, revisit DDR length matching.
2020-04-19 Add power fill zones for VCORE and DDR3 voltages.
2020-04-20 Move +3V3 supply onto PMIC LDO.
    The default configuration of the MXL7704 allows the LDO to be used
    as an always-on supply by controlling the power-on using SEQ_EN in
    place of GLOBAL_EN. Doing so allows us to elminiate another
    regulator.
2020-04-22 Remove STM32 and plan to use an FPGA bootloader instead.
    The MXL7704 is close enough to what the ECP5 needs that we can let
    it boot itself from the OTP and then fixup the voltages once the
    FPGA bootloader starts (the OTP is correct for the ECP5-5G).
2020-04-25 Add a second USB-C port for USB host and SERDES breakout.
    Now that the supervisor is gone, we have a bunch more PCB space which
    we can use to add a USB-C downstream facing port that can serve as a
    USB host and to breakout the extra SERDES channels.
2020-04-26 Replace ADC with a TLA2518
    The previous ADC (STMicor ADC120) was only available in a TSSOP
    package, which was unfortunately too tall to clear a double-sided
    M.2 adaptor card. The TLA2518 comes in a WQFN16 package which is
    much shorter.
2020-04-29 Review BGA pinouts and differential pair tuning. Replace ADC.
    After double-checking the ECP5 pinout, there were a few minor pins that
    got swapped, but nothing that would have damaged anything. We also took
    the time to review the differential pair tuning, and we found that the
    ADC was too tall to clear the M.2 connector.
    Closes: https://github.com/oskirby/logicbone/issues/1
2020-04-29 Tidy up silkscreen, add voltage test points
2020-05-01 Rev0 release to manufacturing.
2020-05-01 Update m.2 3d model to TE-2199230-4.
    It's the same footprint and everything, but with the correct Z-height
    to allow for PCB components on the mainboard.
2020-05-01 Add missing 3D models for crystal and OVP protection.
2020-05-02 Rev0 release to manufacturing (again), due to DDR3 tuning.
    After doing some more review, it turns out that the DDR3 was not
    correctly length matched on the control and address bus. So lets try
    to squeak in a revision that fixes the DDR3 length matching. As a
    side effect, a handful of the pins got swapped around, and the ODT0
    and ODT1 signals got merged.
2020-05-02 Add .gitattributes to fix language detection.
2020-05-02 Update DDR3 timing calculations.
    I forgot to check the updated spreadsheet in after the last few tweaks
    to the DDR3 length matching on the PCB.
2020-05-03 Add BOM, with pricing and links for prototype run.
    For the prototype run, we would like to get two variants of the board
    populated. One with 512MB of RAM and the LFE5UM-45F FPGA, and then a
    souped up version with 2GB of RAM and the LFE5UM5G-85F FPGA.
2020-05-04 Tweak BOM to use ECP5-5G for all variants.
    The price difference between the LFE5UM-45F and the LFE5UM5G-45F is
    only a few dollars, and enables the user to play with USB Superspeed
    and PCIe 2.0, so this just seems like an obvious upgrade. We also
    increase the choice of RAM for the base model to 1GB.
    This also leads to a couple of tweaks in the LDO selection to switch
    the core and SERDES voltages from 1.1V to 1.2V for the 5G models.
2020-06-01 Fix footprint attributes (through hole vs. SMD).
    The footprint attributes determine which parts are exported with the
    position data, which means that several components were missing from
    the last manufacturing package (IC1/2/3, D1, IC6, IC13, J1 and J2).
    This update should set the SMD attributes correctly.
2020-06-27 Add CERN OHL required documentation, annotate schematic.
    The CERN OHL requires the inclusion of a CHANGES.md and a PRODUCT.txt
    file to denote the change history of the project and the contact person
    for production information. While we're at it, we also try to imrpove
    the state of the schematic with explicit copyright and authorship notices
    plus some of the bodges that were added during prototype bringup.
